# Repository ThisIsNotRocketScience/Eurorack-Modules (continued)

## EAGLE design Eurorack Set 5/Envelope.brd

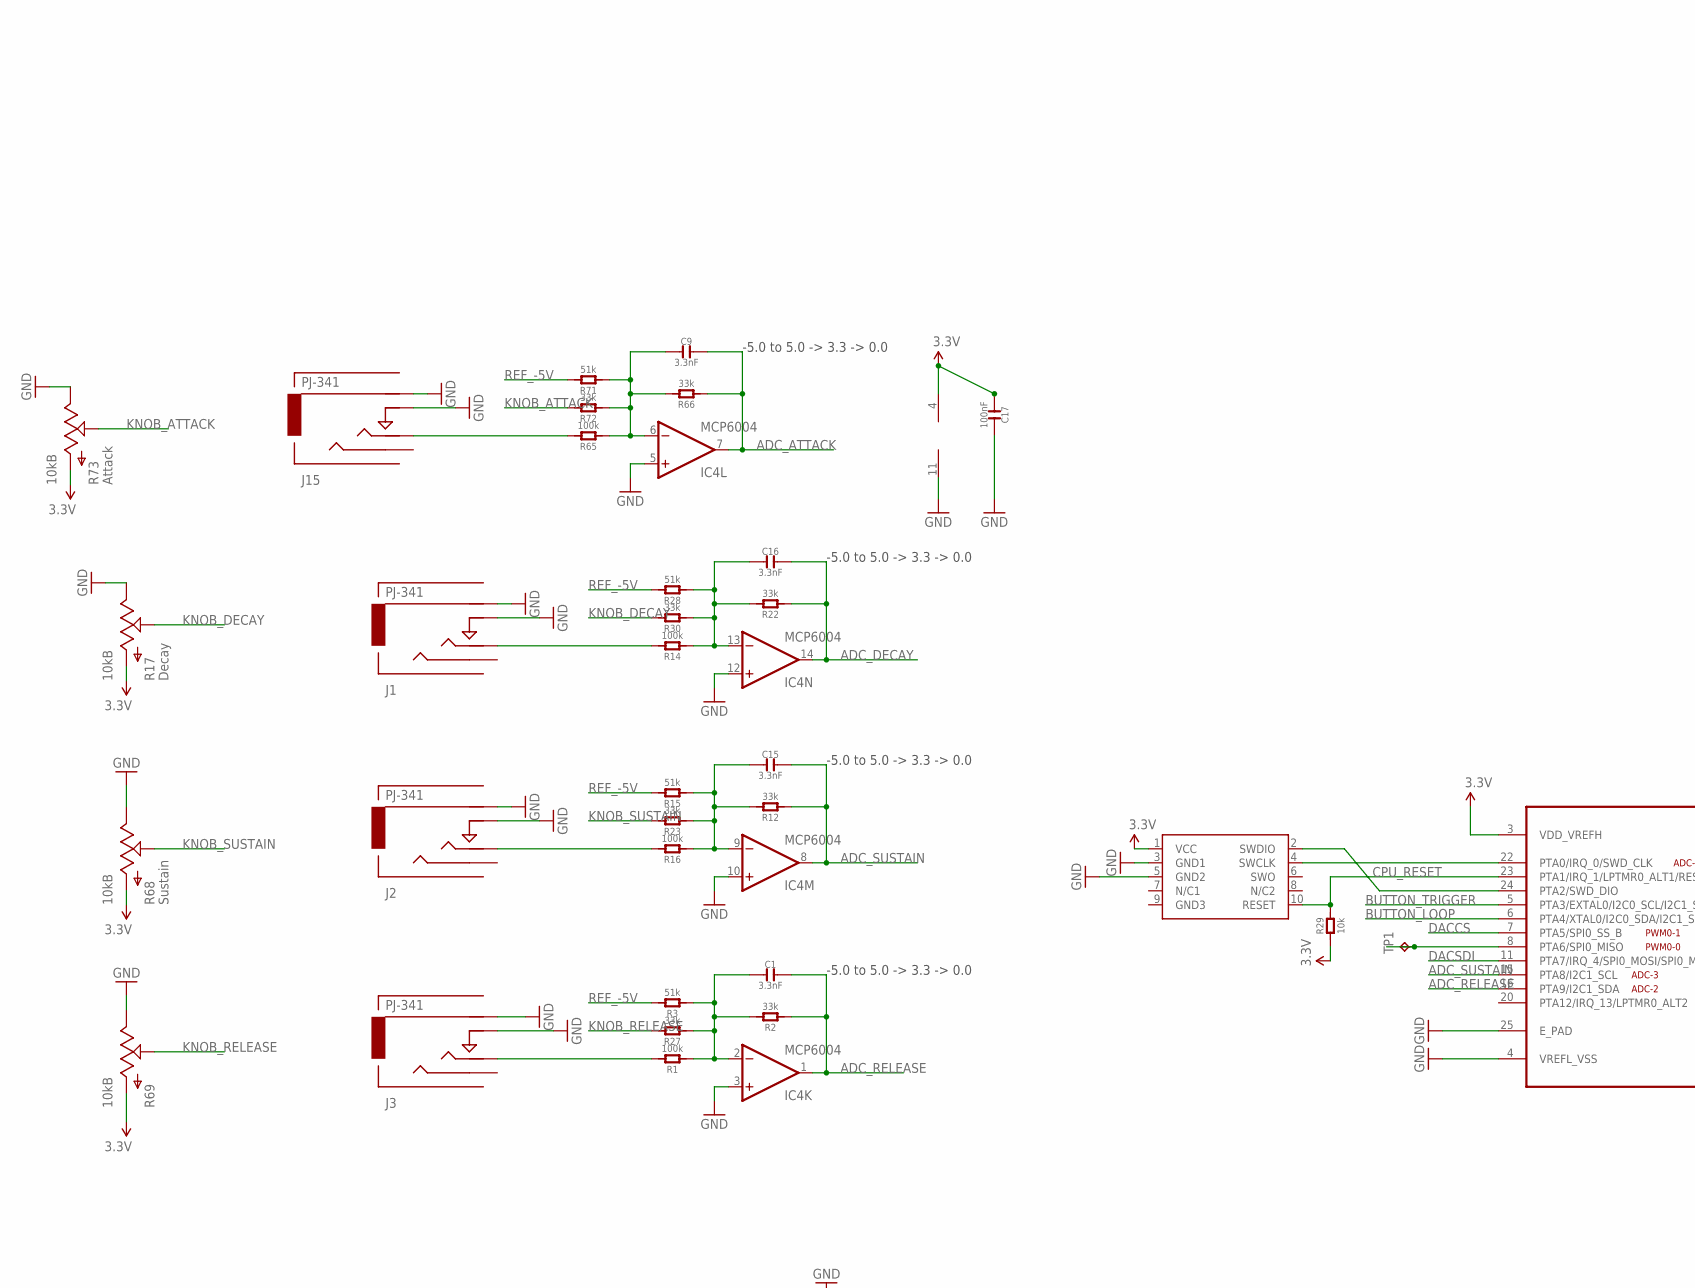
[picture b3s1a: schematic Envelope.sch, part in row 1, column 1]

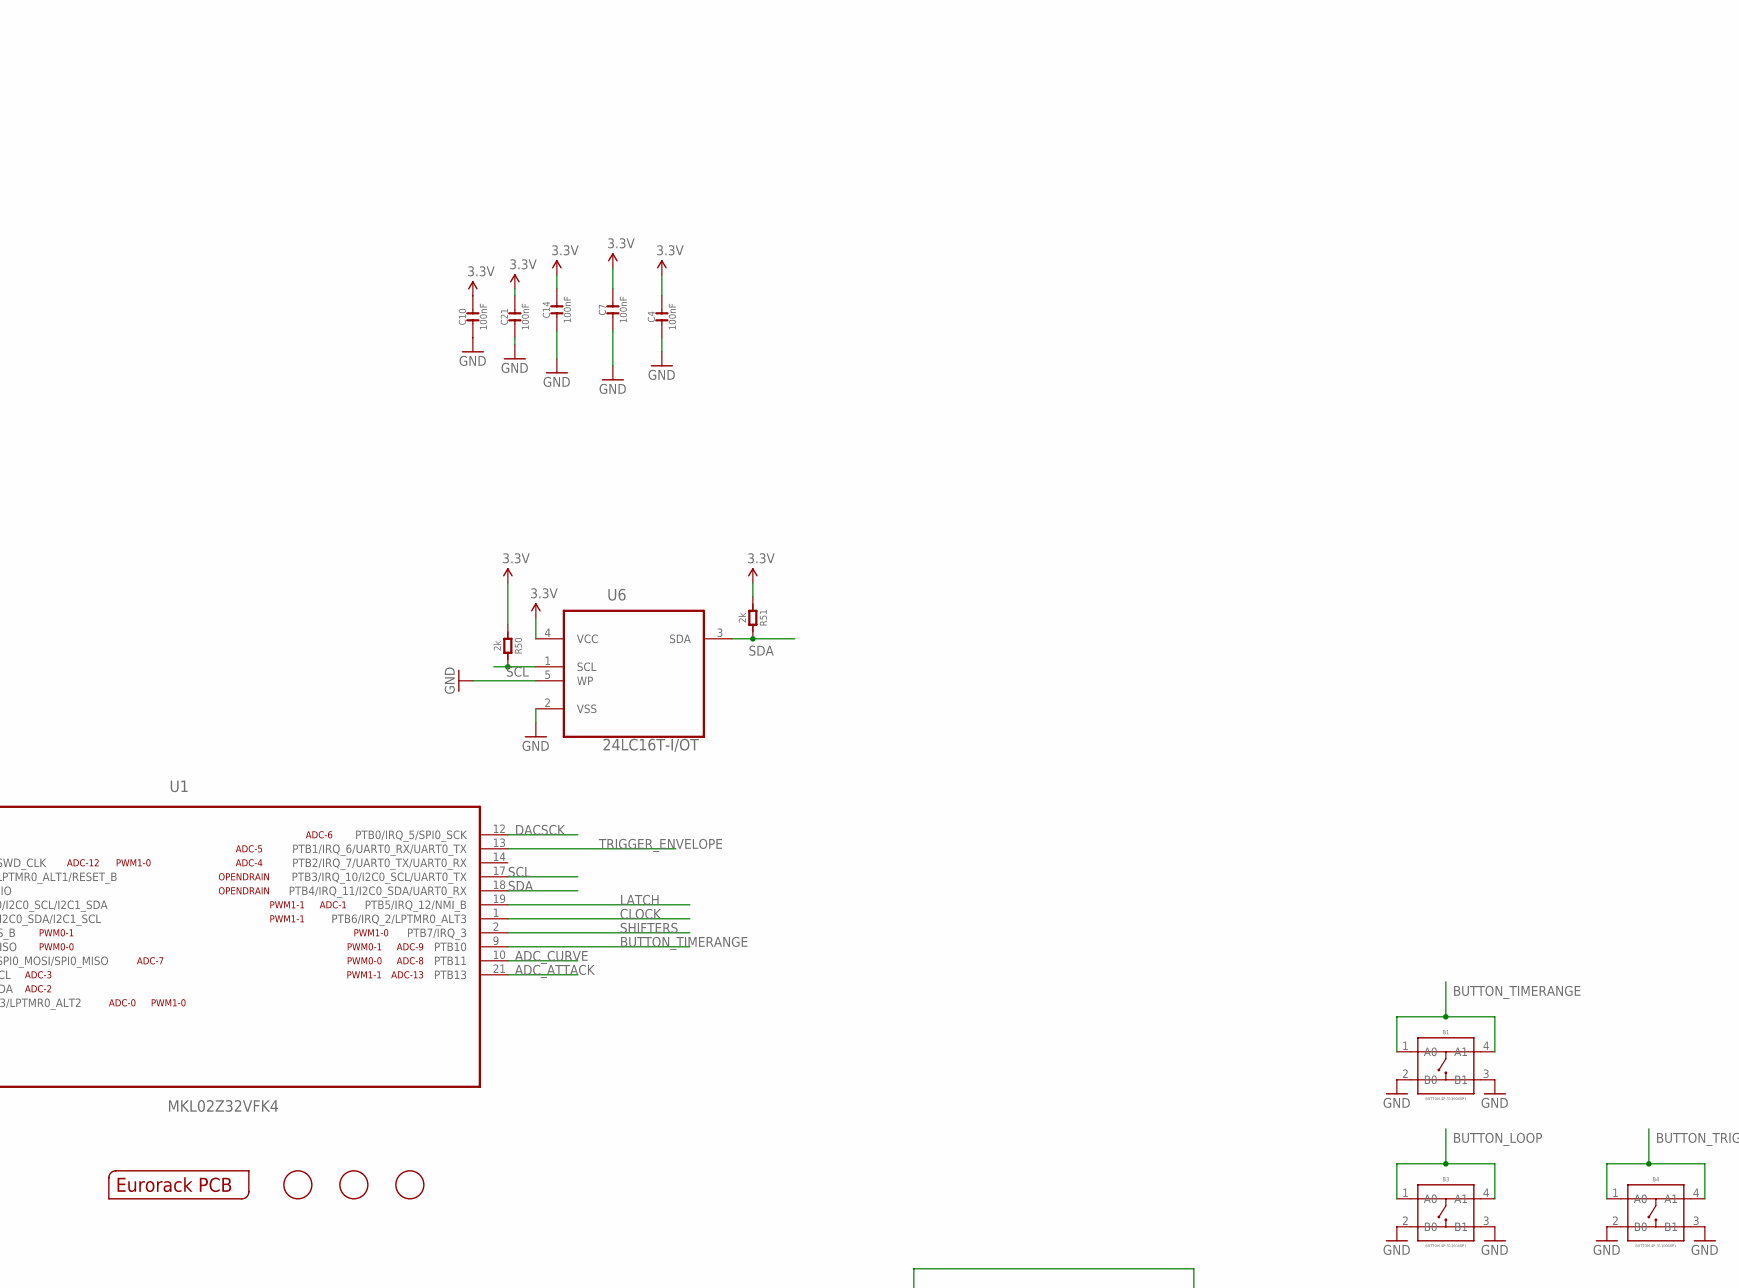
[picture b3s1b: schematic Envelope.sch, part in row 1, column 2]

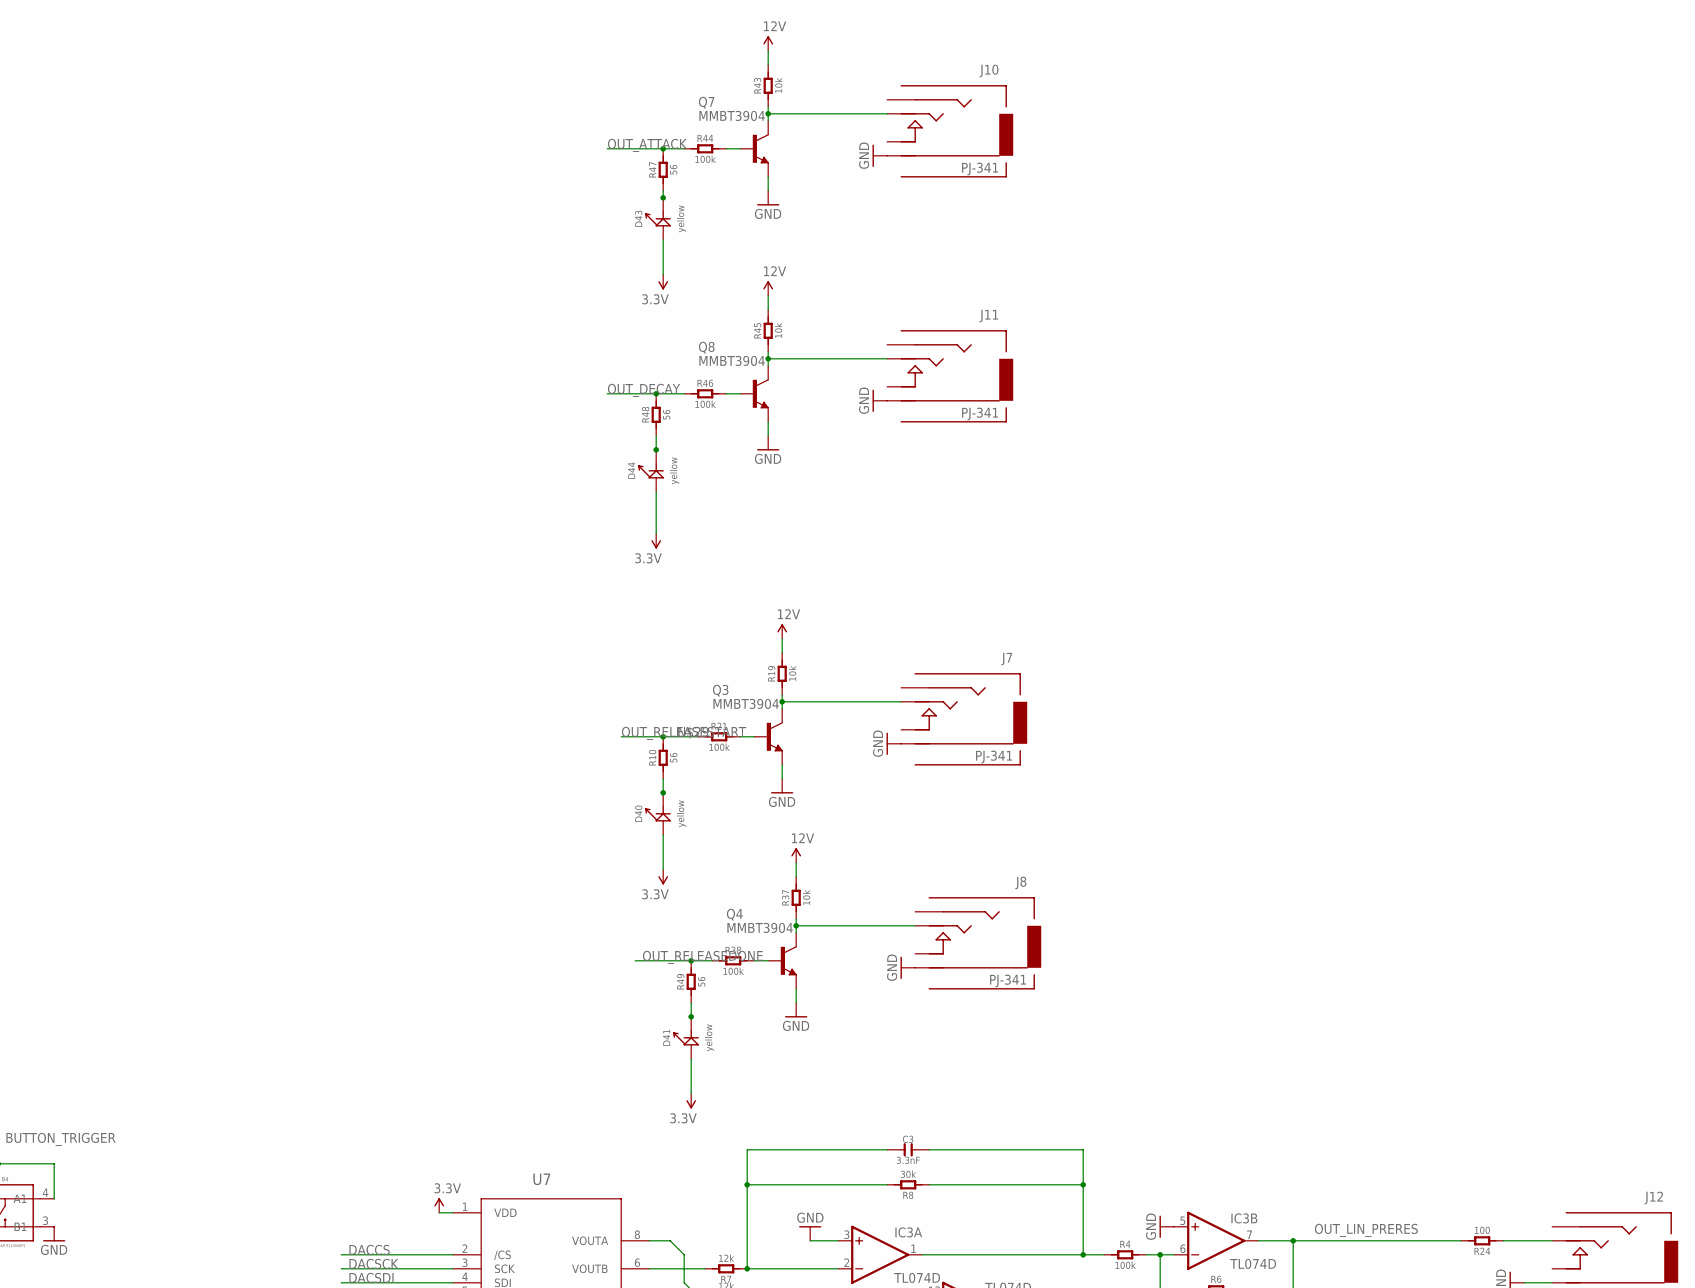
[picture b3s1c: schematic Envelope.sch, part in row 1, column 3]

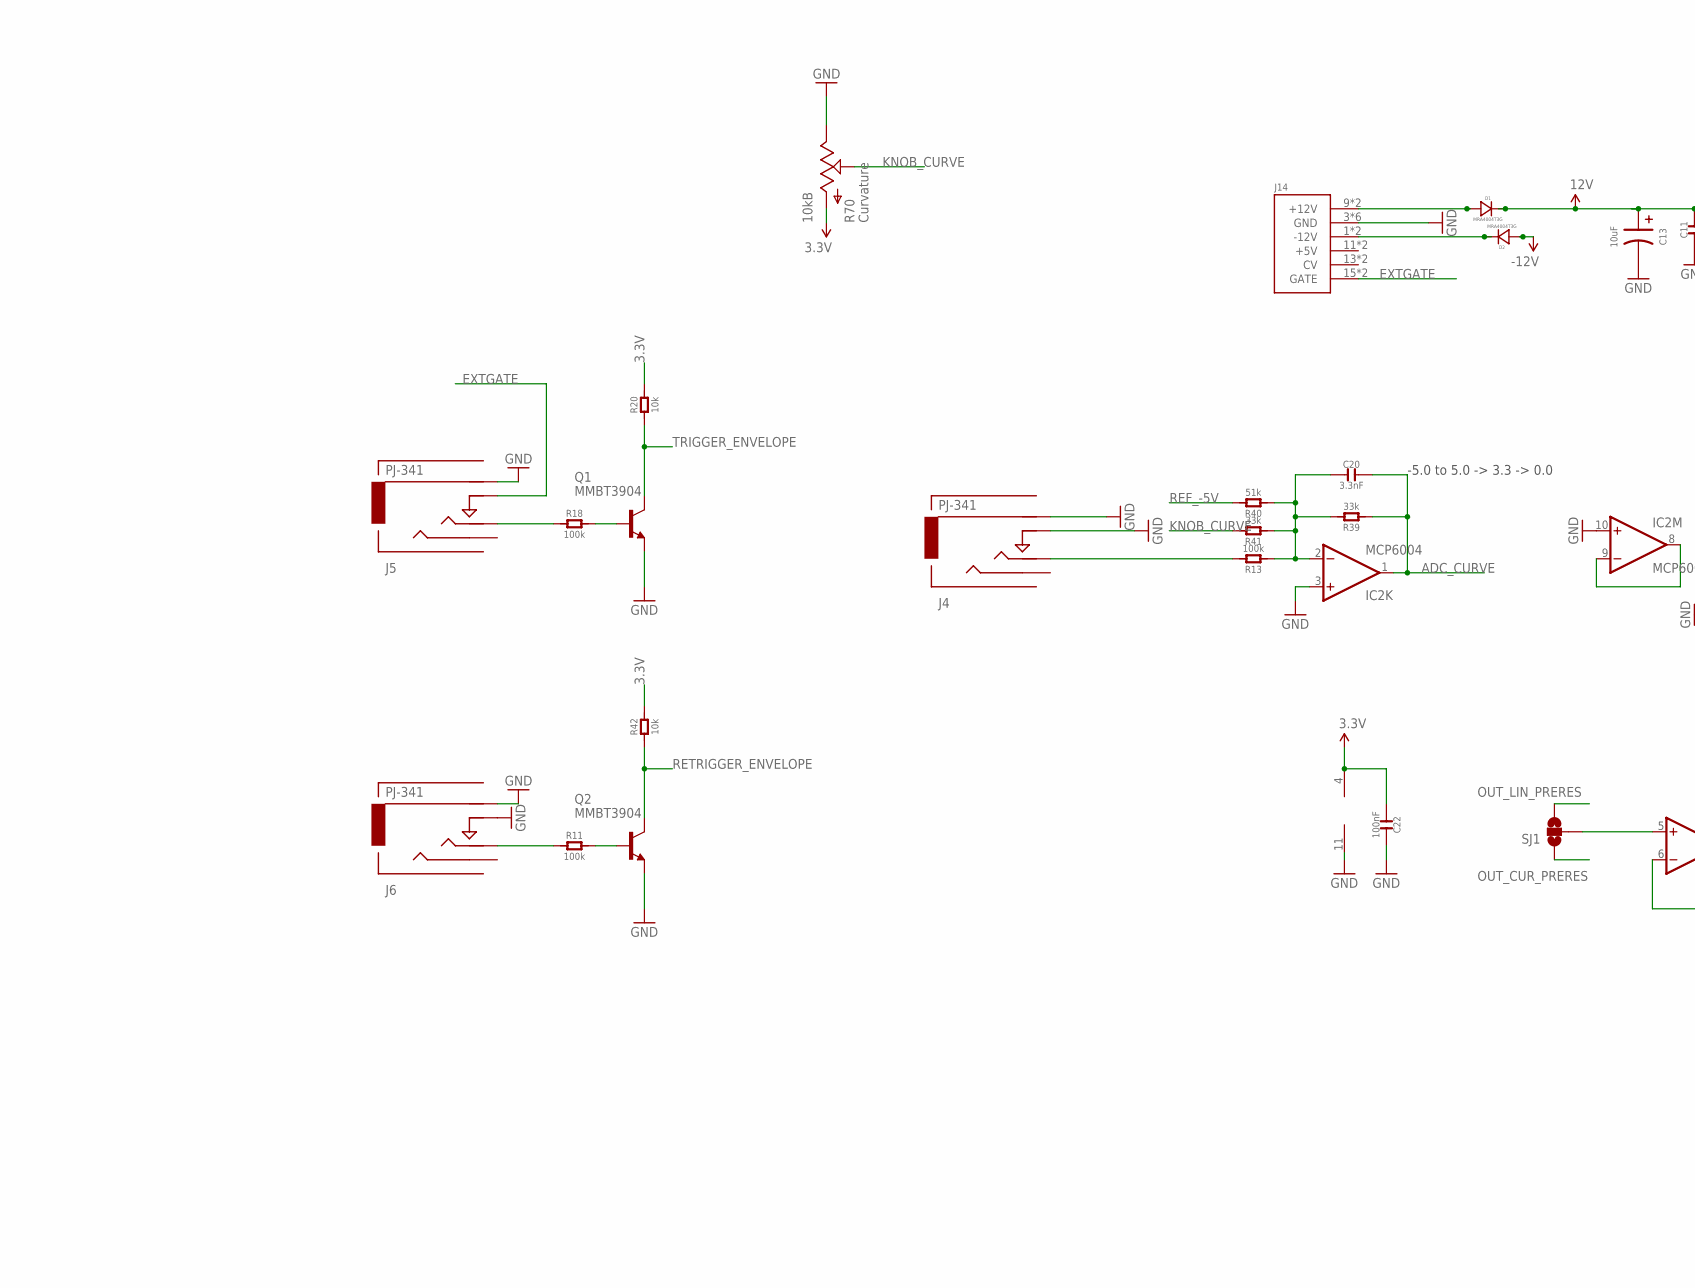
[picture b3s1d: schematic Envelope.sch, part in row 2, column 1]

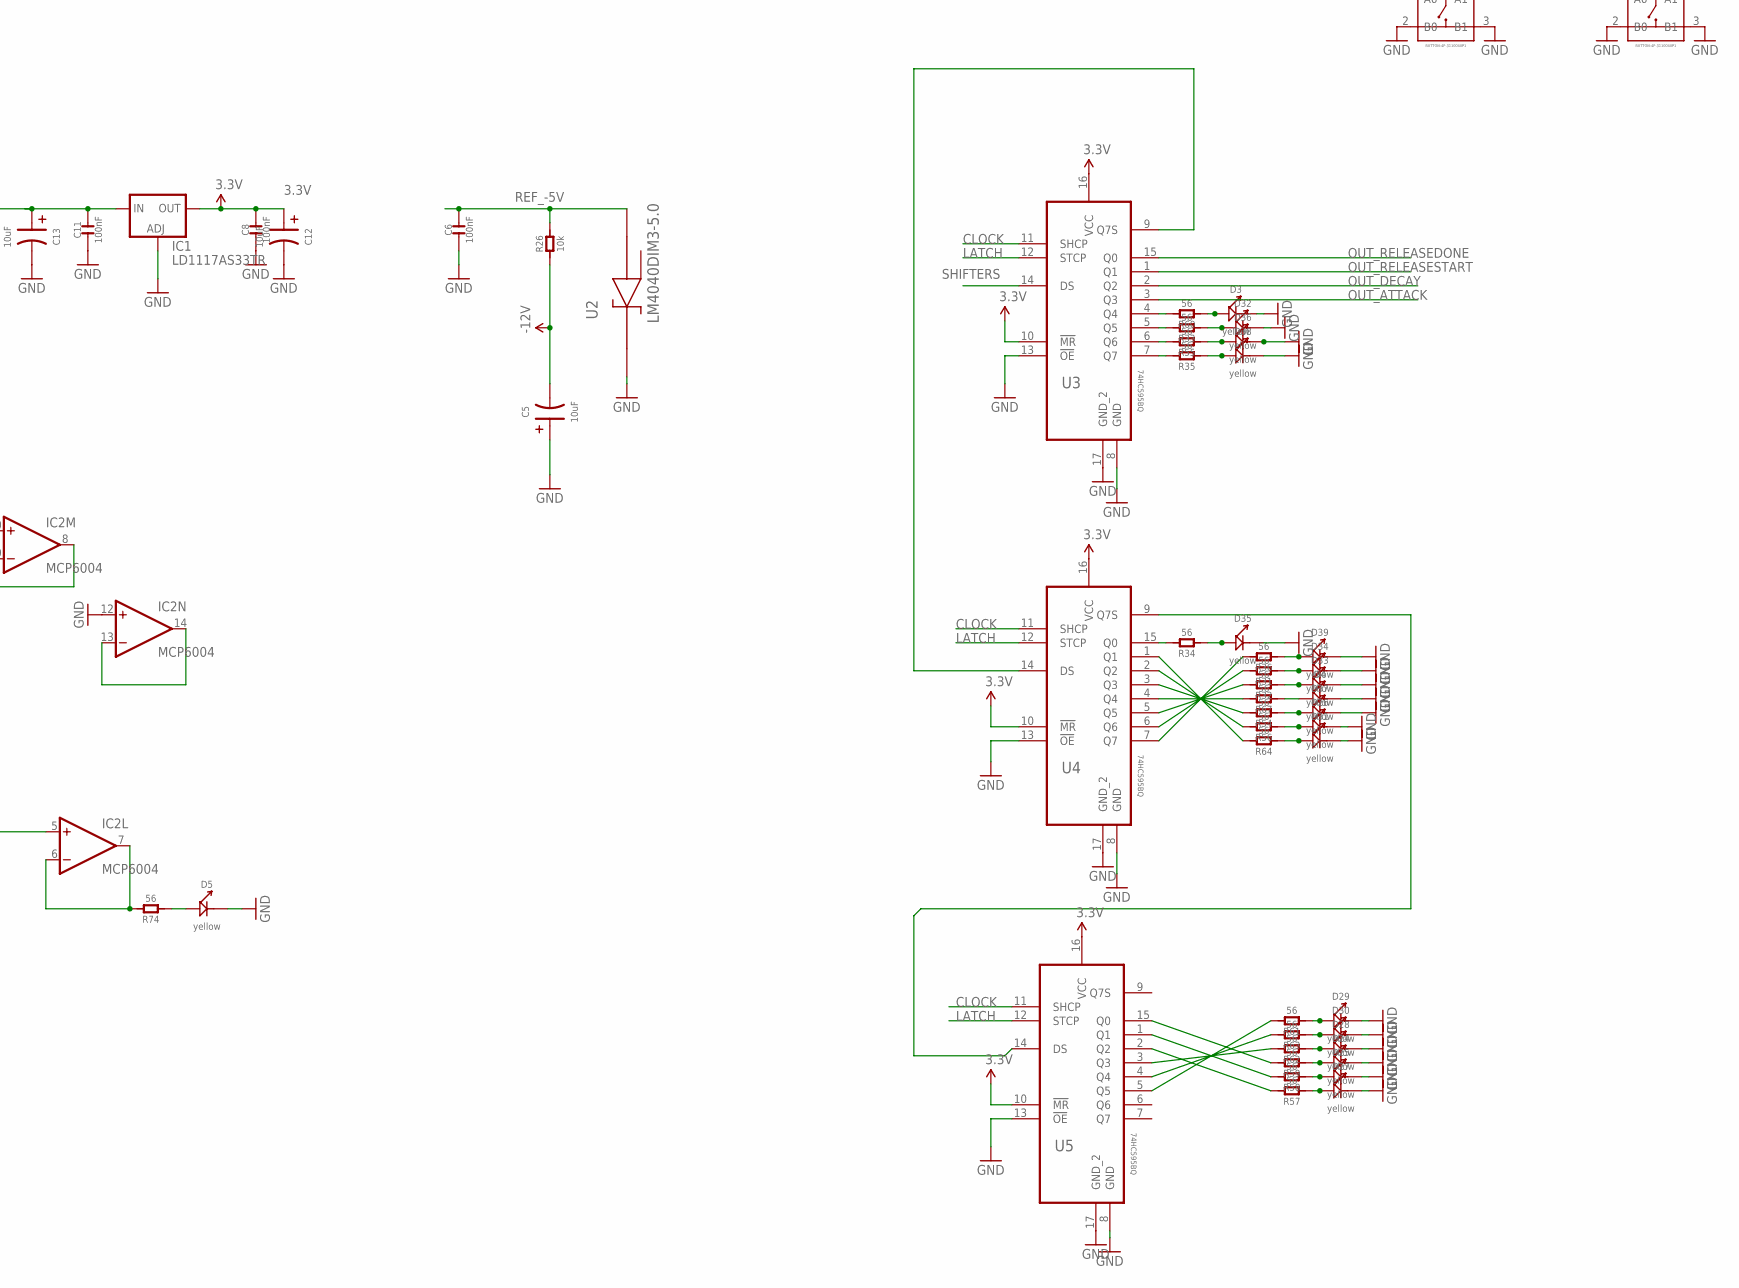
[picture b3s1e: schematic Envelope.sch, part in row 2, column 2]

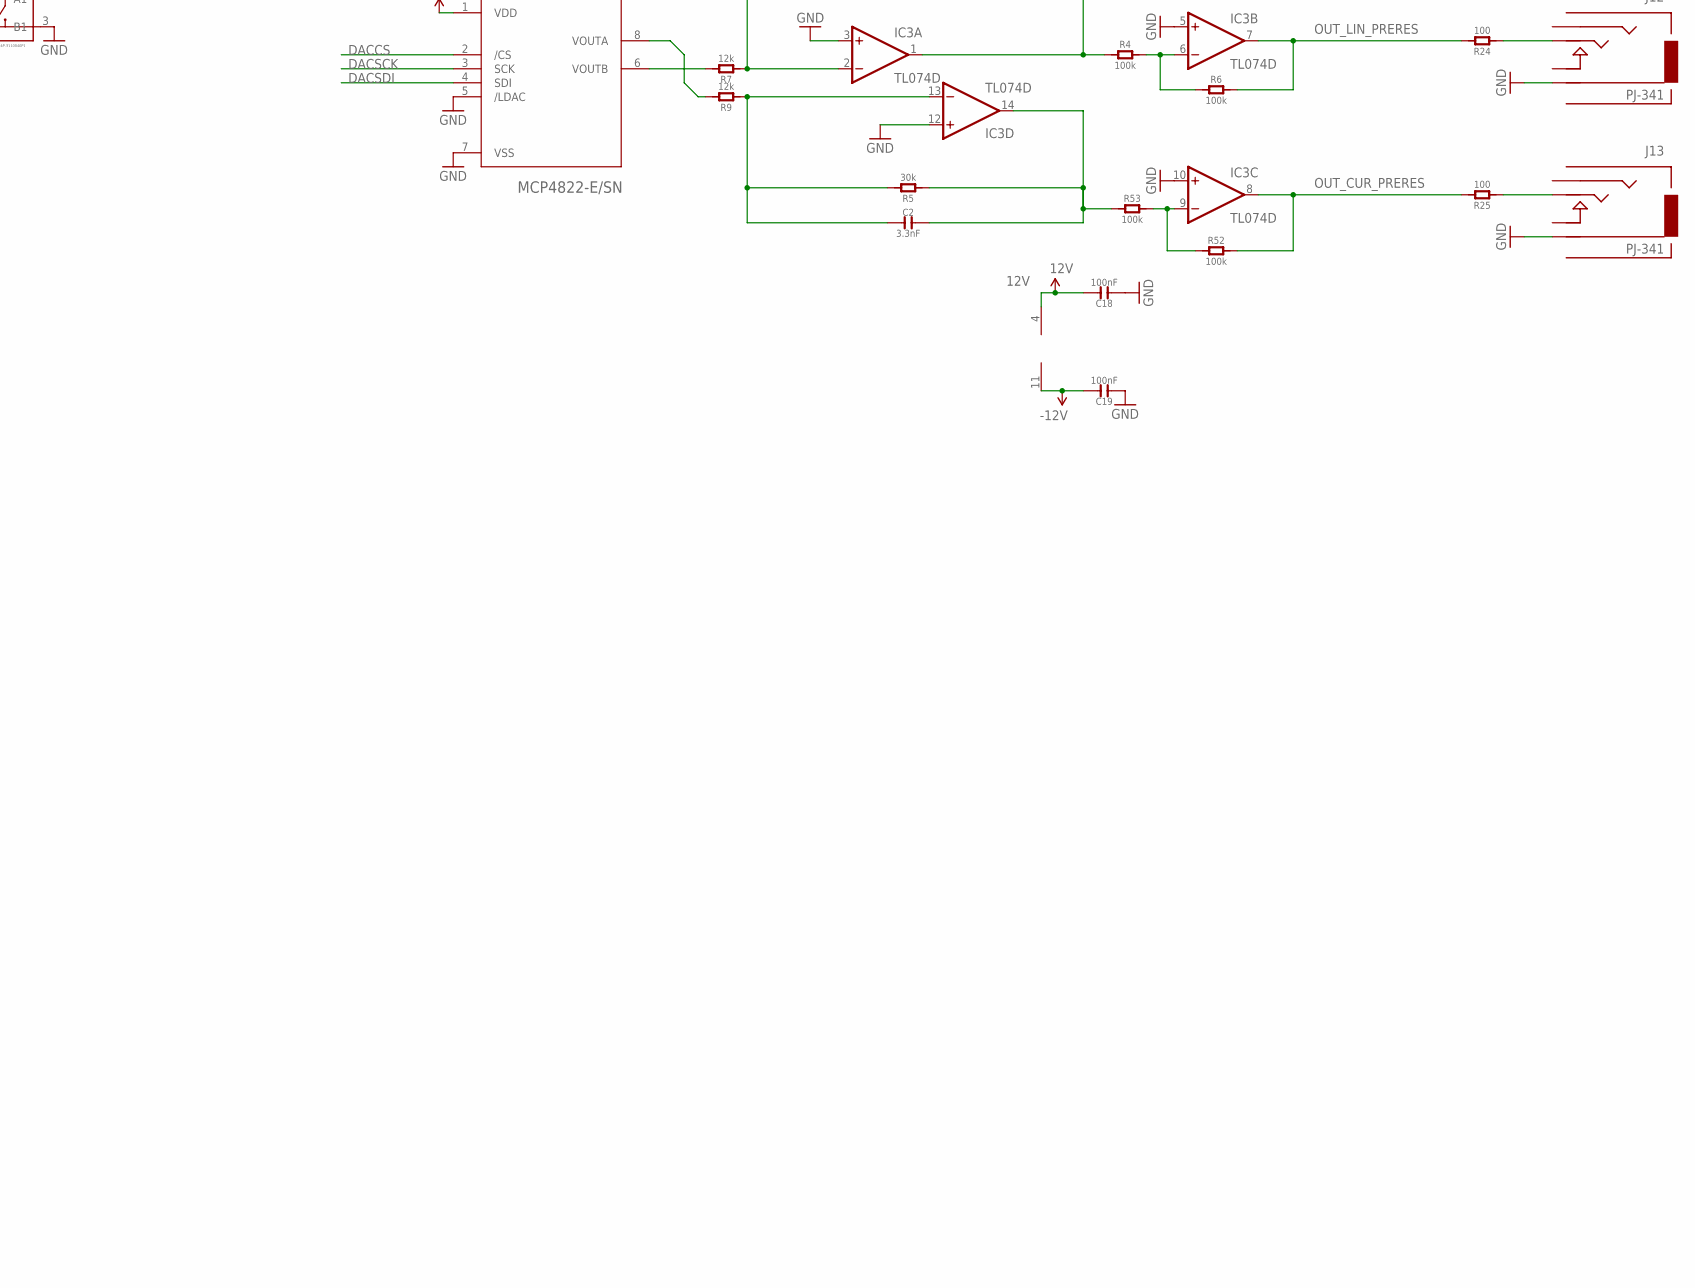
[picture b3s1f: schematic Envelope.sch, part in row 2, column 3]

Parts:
B1, B3, B4: BUTTON-4P-3110040P1; 4P-6.0X6.0X5.0H
C1, C2, C3, C9, C15, C16, C20: 3.3nF; C0603
C4, C7, C8, C10, C11, C14, C17, C18, C19, C21, C22: 100nF; C0603; MPN MC0603F104Z160CT
C5, C12, C13: 10uF; AVX-A; MPN TAJB106K020RNJ
C6: 100nF; C0603; MPN 06035C104KAT2A
D1, D2: MRA4004T3G; DO-214AC; MPN US1G-E3/5AT
D3, D4, D5, D24, D25, D26, D27, D28, D29, D30, D31, D32, D33, D34, D35, D36, D37, D38, D39, D40, D41, D43, D44: yellow; LED0603
FID1, FID2, FID3: FIDUCIAL; FIDUCIAL_1MM
IC1: LD1117AS33TR; SOT223; MPN LD1117AS33TR
IC2, IC4: MCP6004; SO14; MPN MCP6004-I/SL.
IC3: TL074D; SO14; MPN TL074CD
J1, J2, J3, J4, J5, J6, J15: PJ-341; 3.5MM-JACK-SWITCH-13MM-INPUT
J7, J8, J10, J11, J12, J13: PJ-341; 3.5MM-JACK-SWITCH-13MM-OUTPUT
J14: POWER; POWER_16
OUTLINE: EURORACK_PCB12HP; EURORACK12HPPCB
Q1, Q2, Q3, Q4, Q7, Q8: MMBT3904; SOT23-BEC; MPN PMBT3904,215
R1, R4, R6, R11, R13, R14, R16, R18, R21, R38, R44, R46, R52, R53, R65: 100k; R0603
R2, R12, R22, R23, R27, R30, R39, R41, R66, R72: 33k; R0603
R3, R15, R28, R40, R71: 51k; R0603
R5, R8: 30k; R0603
R7, R9: 12k; R0603
R10, R31, R32, R33, R34, R35, R36, R47, R48, R49, R54, R55, R56, R57, R58, R59, R60, R61, R62, R63, R64, R67, R74: 56; R0603
R17, R68, R69, R70, R73: 10kB; OG-POTS_ALPS_POT_VERTICAL
R19, R20, R26, R29, R37, R42, R43, R45: 10k; R0603
R24, R25: 100; R0603
R50, R51: 2k; R0603
SJ1: SOLDERJUMPER_2WAYPASTE1&2; SJ_3_PASTE1&2
SWD1: CORTEX_SWD; M50-3600542
TP1: TPB1,27; B1,27
U1: MKL02Z32VFK4; QFN50P400X400X100-25N
U2: LM4040DIM3-5.0; SOT95P237X112-3N
U3, U4, U5: 74HC595BQ; QFN50P250X350X100-17N
U6: 24LC16T-I/OT; SOT95P290X145-5N; MPN 24LC16T-I/OT
U7: MCP4822-E/SN; SOIC8-N_MC

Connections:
3.3V: C4.2, C7.2, C8.2, C10.2, C12.+ (1), C14.2, C17.1, C21.2, C22.1, D40.+, D41.+, D43.+, D44.+, IC1.2 (OUT), IC1.4 (OUT), IC2.4 (V+), IC4.4 (V+), R17.P$3 (A), R20.2, R29.1, R42.2, R50.1, R51.1, R68.P$3 (A), R69.P$3 (A), R70.P$3 (A), R73.P$3 (A), SWD1.1 (VCC), U1.3 (VDD_VREFH), U3.10 (!MR), U3.16 (VCC), U4.10 (!MR), U4.16 (VCC), U5.10 (!MR), U5.16 (VCC), U6.4 (VCC), U7.1 (VDD)
12V: C11.2, C13.+ (1), C18.2, D1.2 (-), IC1.3 (IN), IC3.4 (V+), R19.2, R37.2, R43.2, R45.2
-12V: C5.- (2), C19.2, D2.1 (+), IC3.11 (V-), R26.1
ADC_ATTACK: C9.2, IC4.7 (OUT), R66.1, U1.21 (PTB13)
ADC_CURVE: C20.2, IC2.1 (OUT), R39.1, U1.10 (PTB11)
ADC_DECAY: C16.2, IC4.14 (OUT), R22.1
ADC_RELEASE: C1.2, IC4.1 (OUT), R2.1, U1.16 (PTA9/I2C1_SDA)
ADC_SUSTAIN: C15.2, IC4.8 (OUT), R12.1, U1.15 (PTA8/I2C1_SCL)
BUTTON_LOOP: B3.1 (A0), B3.4 (A1), U1.6 (PTA4/XTAL0/I2C0_SDA/I2C1_SCL)
BUTTON_TIMERANGE: B1.1 (A0), B1.4 (A1), U1.9 (PTB10)
BUTTON_TRIGGER: B4.1 (A0), B4.4 (A1), U1.5 (PTA3/EXTAL0/I2C0_SCL/I2C1_SDA)
CLOCK: U1.1 (PTB6/IRQ_2/LPTMR0_ALT3), U3.11 (SHCP), U4.11 (SHCP), U5.11 (SHCP)
CPU_RESET: R29.2, SWD1.10 (RESET), U1.23 (PTA1/IRQ_1/LPTMR0_ALT1/RESET_B)
D21: D43.-, R47.1
DACCS: U1.7 (PTA5/SPI0_SS_B), U7.2 (/CS)
DACSCK: U1.12 (PTB0/IRQ_5/SPI0_SCK), U7.3 (SCK)
DACSDI: U1.11 (PTA7/IRQ_4/SPI0_MOSI/SPI0_MISO), U7.4 (SDI)
EXTGATE: J5.SWITCH@3 (SWITCH), J14.15 (GATE), J14.16 (GATE)
GND: B1.2 (B0), B1.3 (B1), B3.2 (B0), B3.3 (B1), B4.2 (B0), B4.3 (B1), C4.1, C5.+ (1), C6.1, C7.1, C8.1, C10.1, C11.1, C12.- (2), C13.- (2), C14.1, C17.2, C18.1, C19.1, C21.1, C22.2, D3.-, D4.-, D5.-, D24.-, D25.-, D26.-, D27.-, D28.-, D29.-, D30.-, D31.-, D32.-, D33.-, D34.-, D35.-, D36.-, D37.-, D38.-, D39.-, IC1.1 (ADJ), IC2.3 (+IN), IC2.10 (+IN), IC2.11 (V-), IC2.12 (+IN), IC3.3 (+IN), IC3.5 (+IN), IC3.10 (+IN), IC3.12 (+IN), IC4.3 (+IN), IC4.5 (+IN), IC4.10 (+IN), IC4.11 (V-), IC4.12 (+IN), J1.RING@3 (RING), J1.SWITCH@3 (SWITCH), J2.RING@3 (RING), J2.SWITCH@3 (SWITCH), J3.RING@3 (RING), J3.SWITCH@3 (SWITCH), J4.RING@3 (RING), J4.SWITCH@3 (SWITCH), J5.RING@3 (RING), J6.RING@3 (RING), J6.SWITCH@3 (SWITCH), J7.RING@3 (RING), J8.RING@3 (RING), J10.RING@3 (RING), J11.RING@3 (RING), J12.RING@3 (RING), J13.RING@3 (RING), J14.3 (GND), J14.4 (GND), J14.5 (GND), J14.6 (GND), J14.7 (GND), J14.8 (GND), J15.RING@3 (RING), J15.SWITCH@3 (SWITCH), Q1.E, Q2.E, Q3.E, Q4.E, Q7.E, Q8.E, R17.P$1 (E), R68.P$1 (E), R69.P$1 (E), R70.P$1 (E), R73.P$1 (E), SWD1.3 (GND1), SWD1.5 (GND2), U1.4 (VREFL_VSS), U1.25 (E_PAD), U2.1 (CATHODE), U3.8 (GND), U3.13 (!OE), U3.17 (GND_2), U4.8 (GND), U4.13 (!OE), U4.17 (GND_2), U5.8 (GND), U5.13 (!OE), U5.17 (GND_2), U6.2 (VSS), U6.5 (WP), U7.5 (/LDAC), U7.7 (VSS)
KNOB_ATTACK: R72.2, R73.P$2 (S)
KNOB_CURVE: R41.2, R70.P$2 (S)
KNOB_DECAY: R17.P$2 (S), R30.2
KNOB_RELEASE: R27.2, R69.P$2 (S)
KNOB_SUSTAIN: R23.2, R68.P$2 (S)
LATCH: U1.19 (PTB5/IRQ_12/NMI_B), U3.12 (STCP), U4.12 (STCP), U5.12 (STCP)
unnamed: IC2.8 (OUT), IC2.9 (-IN)
unnamed: IC3.6 (-IN), R4.2, R6.1
unnamed: J2.TIP@3 (TIP), R16.2
unnamed: C15.1, IC4.9 (-IN), R12.2, R15.1, R16.1, R23.1
unnamed: R9.2, U7.8 (VOUTA)
unnamed: J3.TIP@3 (TIP), R1.2
unnamed: R7.2, U7.6 (VOUTB)
unnamed: C1.1, IC4.2 (-IN), R1.1, R2.2, R3.1, R27.1
unnamed: C2.1, IC3.13 (-IN), R5.2, R9.1
unnamed: C3.1, IC3.2 (-IN), R7.1, R8.2
unnamed: J15.TIP@3 (TIP), R65.2
unnamed: J4.TIP@3 (TIP), R13.2
unnamed: D1.1 (+), J14.9 (+12V), J14.10 (+12V)
unnamed: R36.2, U4.7 (Q7)
unnamed: Q1.B, R18.2
unnamed: J5.TIP@3 (TIP), R18.1
unnamed: IC3.9 (-IN), R52.1, R53.2
unnamed: C3.2, IC3.1 (OUT), R4.1, R8.1
unnamed: IC2.6 (-IN), IC2.7 (OUT), R74.2
unnamed: J13.TIP@3 (TIP), R25.1
unnamed: J12.TIP@3 (TIP), R24.1
unnamed: C9.1, IC4.6 (-IN), R65.1, R66.2, R71.1, R72.1
unnamed: D40.-, R10.1
unnamed: C2.2, IC3.14 (OUT), R5.1, R53.1
unnamed: Q3.B, R21.2
unnamed: IC2.13 (-IN), IC2.14 (OUT)
unnamed: R31.2, U4.6 (Q6)
unnamed: D28.+, R62.1
unnamed: J7.TIP@3 (TIP), Q3.C, R19.1
unnamed: D4.+, R67.1
unnamed: R60.2, U3.4 (Q4)
unnamed: D29.+, R61.1
unnamed: J1.TIP@3 (TIP), R14.2
unnamed: C16.1, IC4.13 (-IN), R14.1, R22.2, R28.1, R30.1
unnamed: R33.2, U3.5 (Q5)
unnamed: R55.2, U3.6 (Q6)
unnamed: R35.2, U3.7 (Q7)
unnamed: R34.2, U4.15 (Q0)
unnamed: R32.2, U4.5 (Q5)
unnamed: R67.2, U4.4 (Q4)
unnamed: R54.2, U4.3 (Q3)
unnamed: R56.2, U4.2 (Q2)
unnamed: Q2.B, R11.2
unnamed: D41.-, R49.1
unnamed: D44.-, R48.1
unnamed: C20.1, IC2.2 (-IN), R13.1, R39.2, R40.1, R41.1
unnamed: J6.TIP@3 (TIP), R11.1
unnamed: R64.2, U4.1 (Q1)
unnamed: R61.2, U5.5 (Q5)
unnamed: R59.2, U5.15 (Q0)
unnamed: D3.+, R60.1
unnamed: R58.2, U5.1 (Q1)
unnamed: R57.2, U5.2 (Q2)
unnamed: R62.2, U5.3 (Q3)
unnamed: R63.2, U5.4 (Q4)
unnamed: Q4.B, R38.2
unnamed: J8.TIP@3 (TIP), Q4.C, R37.1
unnamed: D5.+, R74.1
unnamed: IC2.5 (+IN), SJ1.2
unnamed: D2.2 (-), J14.1 (-12V), J14.2 (-12V)
unnamed: Q7.B, R44.2
unnamed: J10.TIP@3 (TIP), Q7.C, R43.1
unnamed: Q8.B, R46.2
unnamed: J11.TIP@3 (TIP), Q8.C, R45.1
unnamed: D27.+, R57.1
unnamed: D26.+, R56.1
unnamed: D25.+, R58.1
unnamed: D24.+, R59.1
unnamed: D30.+, R63.1
unnamed: D31.+, R64.1
unnamed: D32.+, R33.1
unnamed: D33.+, R32.1
unnamed: D34.+, R31.1
unnamed: D35.+, R34.1
unnamed: D36.+, R55.1
unnamed: D37.+, R54.1
unnamed: D38.+, R35.1
unnamed: D39.+, R36.1
OUT_ATTACK: R44.1, R47.2, U3.3 (Q3)
OUT_CUR_PRERES: IC3.8 (OUT), R25.2, R52.2, SJ1.1
OUT_DECAY: R46.1, R48.2, U3.2 (Q2)
OUT_LIN_PRERES: IC3.7 (OUT), R6.2, R24.2, SJ1.3
OUT_RELEASEDONE: R38.1, R49.2, U3.15 (Q0)
OUT_RELEASESTART: R10.2, R21.1, U3.1 (Q1)
PTA6: TP1.TP, U1.8 (PTA6/SPI0_MISO)
REF_-5V: C6.2, R3.2, R15.2, R26.2, R28.2, R40.2, R71.2, U2.2 (ANODE)
RETRIGGER_ENVELOPE: Q2.C, R42.1
SCL: R50.2, U1.17 (PTB3/IRQ_10/I2C0_SCL/UART0_TX), U6.1 (SCL)
SDA: R51.2, U1.18 (PTB4/IRQ_11/I2C0_SDA/UART0_RX), U6.3 (SDA)
SHIFTER1TO2: U3.9 (Q7S), U4.14 (DS)
SHIFTER2TO3: U4.9 (Q7S), U5.14 (DS)
SHIFTERS: U1.2 (PTB7/IRQ_3), U3.14 (DS)
SWD_CLK: SWD1.4 (SWCLK), U1.22 (PTA0/IRQ_0/SWD_CLK)
SWD_DIO: SWD1.2 (SWDIO), U1.24 (PTA2/SWD_DIO)
TRIGGER_ENVELOPE: Q1.C, R20.1, U1.13 (PTB1/IRQ_6/UART0_RX/UART0_TX)

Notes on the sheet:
-5.0 to 5.0 -> 3.3 -> 0.0

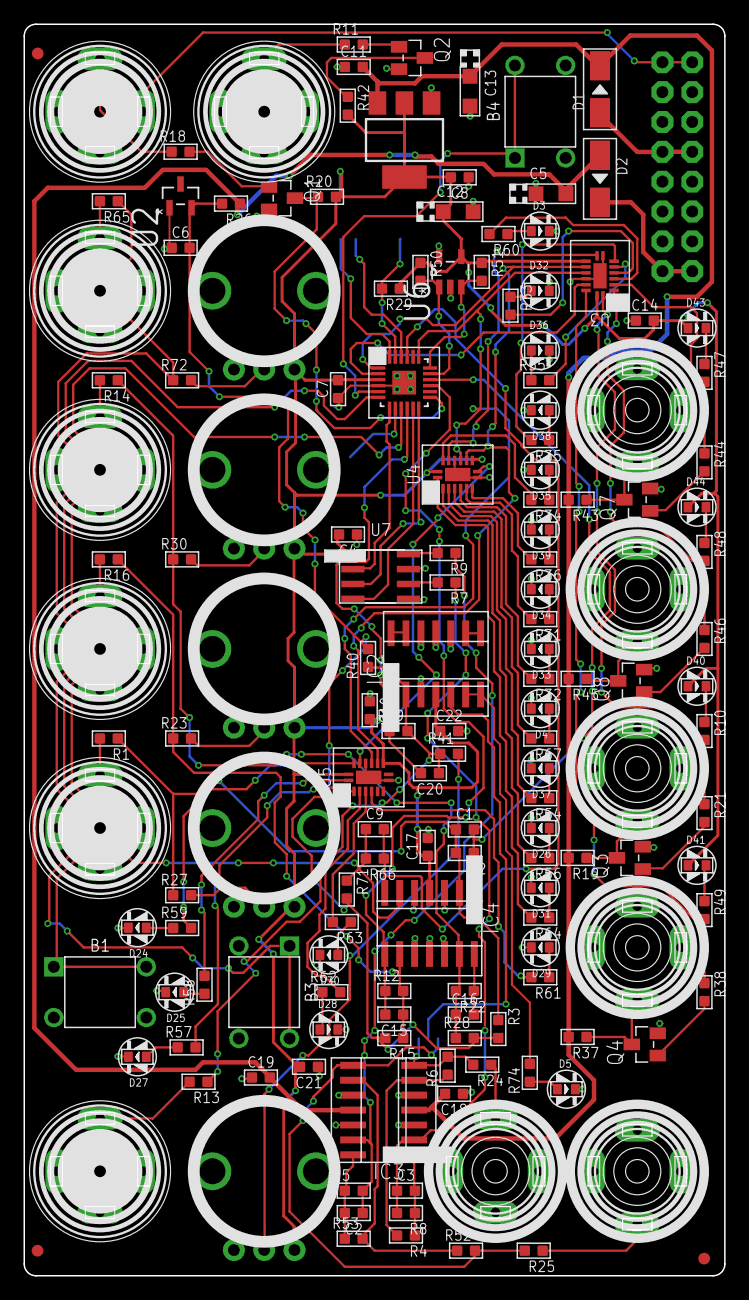
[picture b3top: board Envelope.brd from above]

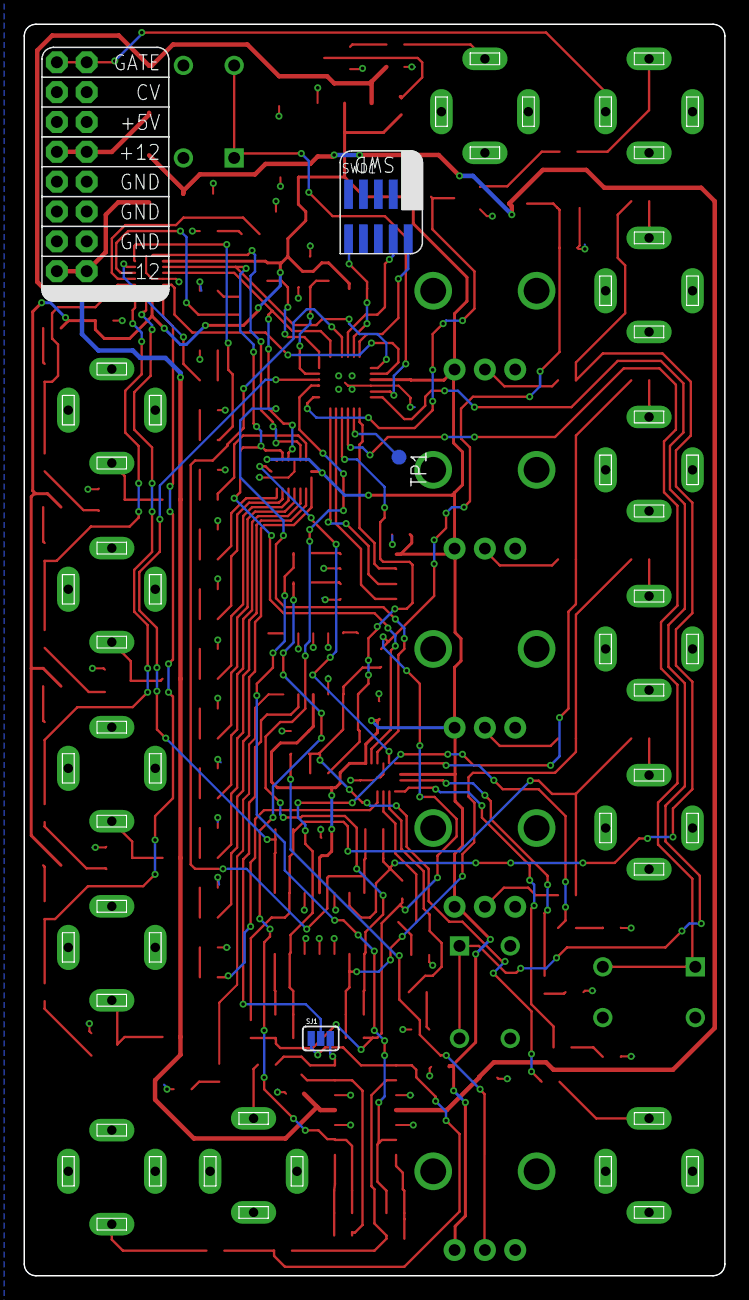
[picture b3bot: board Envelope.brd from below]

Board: 2 copper layers, 59.6 x 106.5 mm, 162 parts (4 on the bottom side), 120 nets.
